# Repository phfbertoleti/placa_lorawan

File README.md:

# Placa LoRaWAN - repositório oficial

Este é o repositório oficial da placa LoRaWAN, placa de desenvolvimento para protótipos em Internet das Coisas com LoRaWAN, Bluetooth (BLE e clássico) e WiFi, fazendo uso do módulo Heltec wifi LoRa V1.

Este projeto é totalmente open-source (licença: MIT).

## Princípio de funcionamento

Essa placa tem objetivo de facilitar o desenvolvimento de protótipos em Internet das Coisas. A melhor forma encontrada para facilitar isso, foi disponibilizar conexões / soquetes para módulo de controle (Heltec wifi LoRa V1) e módulos sensores, conforme a seguir:

* Módulo MPU6050
* Módulo BMP180
* Módulo INA219
* Módulo MQ-2

Para comunicação com módulos (exemplo: GPS) e microcontroladores externos, a placa conta ainda com uma interface UART (níveis 3V3 e 5V, selecionável por jumper / ponte soldada na placa) e uma interface I²C (nível 3V3).

Além disso, essa placa permite o uso do módulo de controle Heltec wifi LoRa V1 com bateria (LiPo ou Li-Ion, de 1 célula), permitindo também a recarga e medição da tensão da mesma.

Isso significa que mesmo que você possua pouca experiência com eletrônica e soldagem, conseguirá facilmente montar e utilizar a placa.

## Funcionalidades

Esta placa, usada juntamente com um módulo Heltec wifi LoRa V1 e os sensores que a placa suporta, compreende as seguintes funcionaliades:
 
* Conectividades wifi, Bluetooth (BLE e clássico), LoRa e LoRaWAN.
* Medição de temperatura
* Medição de pressão barométrica
* Medição de aceleração (3 eixos)
* Giroscópio (3 eixos)
* Tensão e corrente DC
* Detecção de gases inflamávei e fumaça
* Display OLED 0.96" (azul)

Além disso, a placa possui conector para alimentação através de energias renováveis (solar, eólica ou hidráulica), com tensão de alimentação de até 15V.

## O que está disponivel neste repositório?

Resposta curta: 100% do projeto. Ou seja:

* Projeto completo de hardware (feito no KiCad 5.1.5)
* Arquivos gerber, já nos padrões para fabricação exigidos pela JLCPCB (www.jlcpcb.com)
* Softwares de exemplo (todos feitos na Arduino IDE, fazendo uso de bibliotecas populares e consagradas)
* Lista de materiais (BOM)
* Bibliotecas e footprints KiCad (para transistor FQP30N06L e Heltec wifi LoRa V1, sendo este último desenhado por mim).

Para ver a BOM interativa, [clique aqui](https://htmlpreview.github.io/?https://github.com/phfbertoleti/placa_lorawan/blob/master/BOM/ibom.html)

## Desejo contribuir com novas funcionalidades ou correções. Sou bem vindo?

Claro. Sinta-se a vontade para contribuir com o projeto. Toda melhoria é bem vinda!

## Gostei do seu trabalho. Onde consigo mais coisas publicadas por você?

Visite meu [site pessoal](http://www.pedrobertoleti.com.br) para ter acesso a quase tudo que publico no Brasil e exterior.

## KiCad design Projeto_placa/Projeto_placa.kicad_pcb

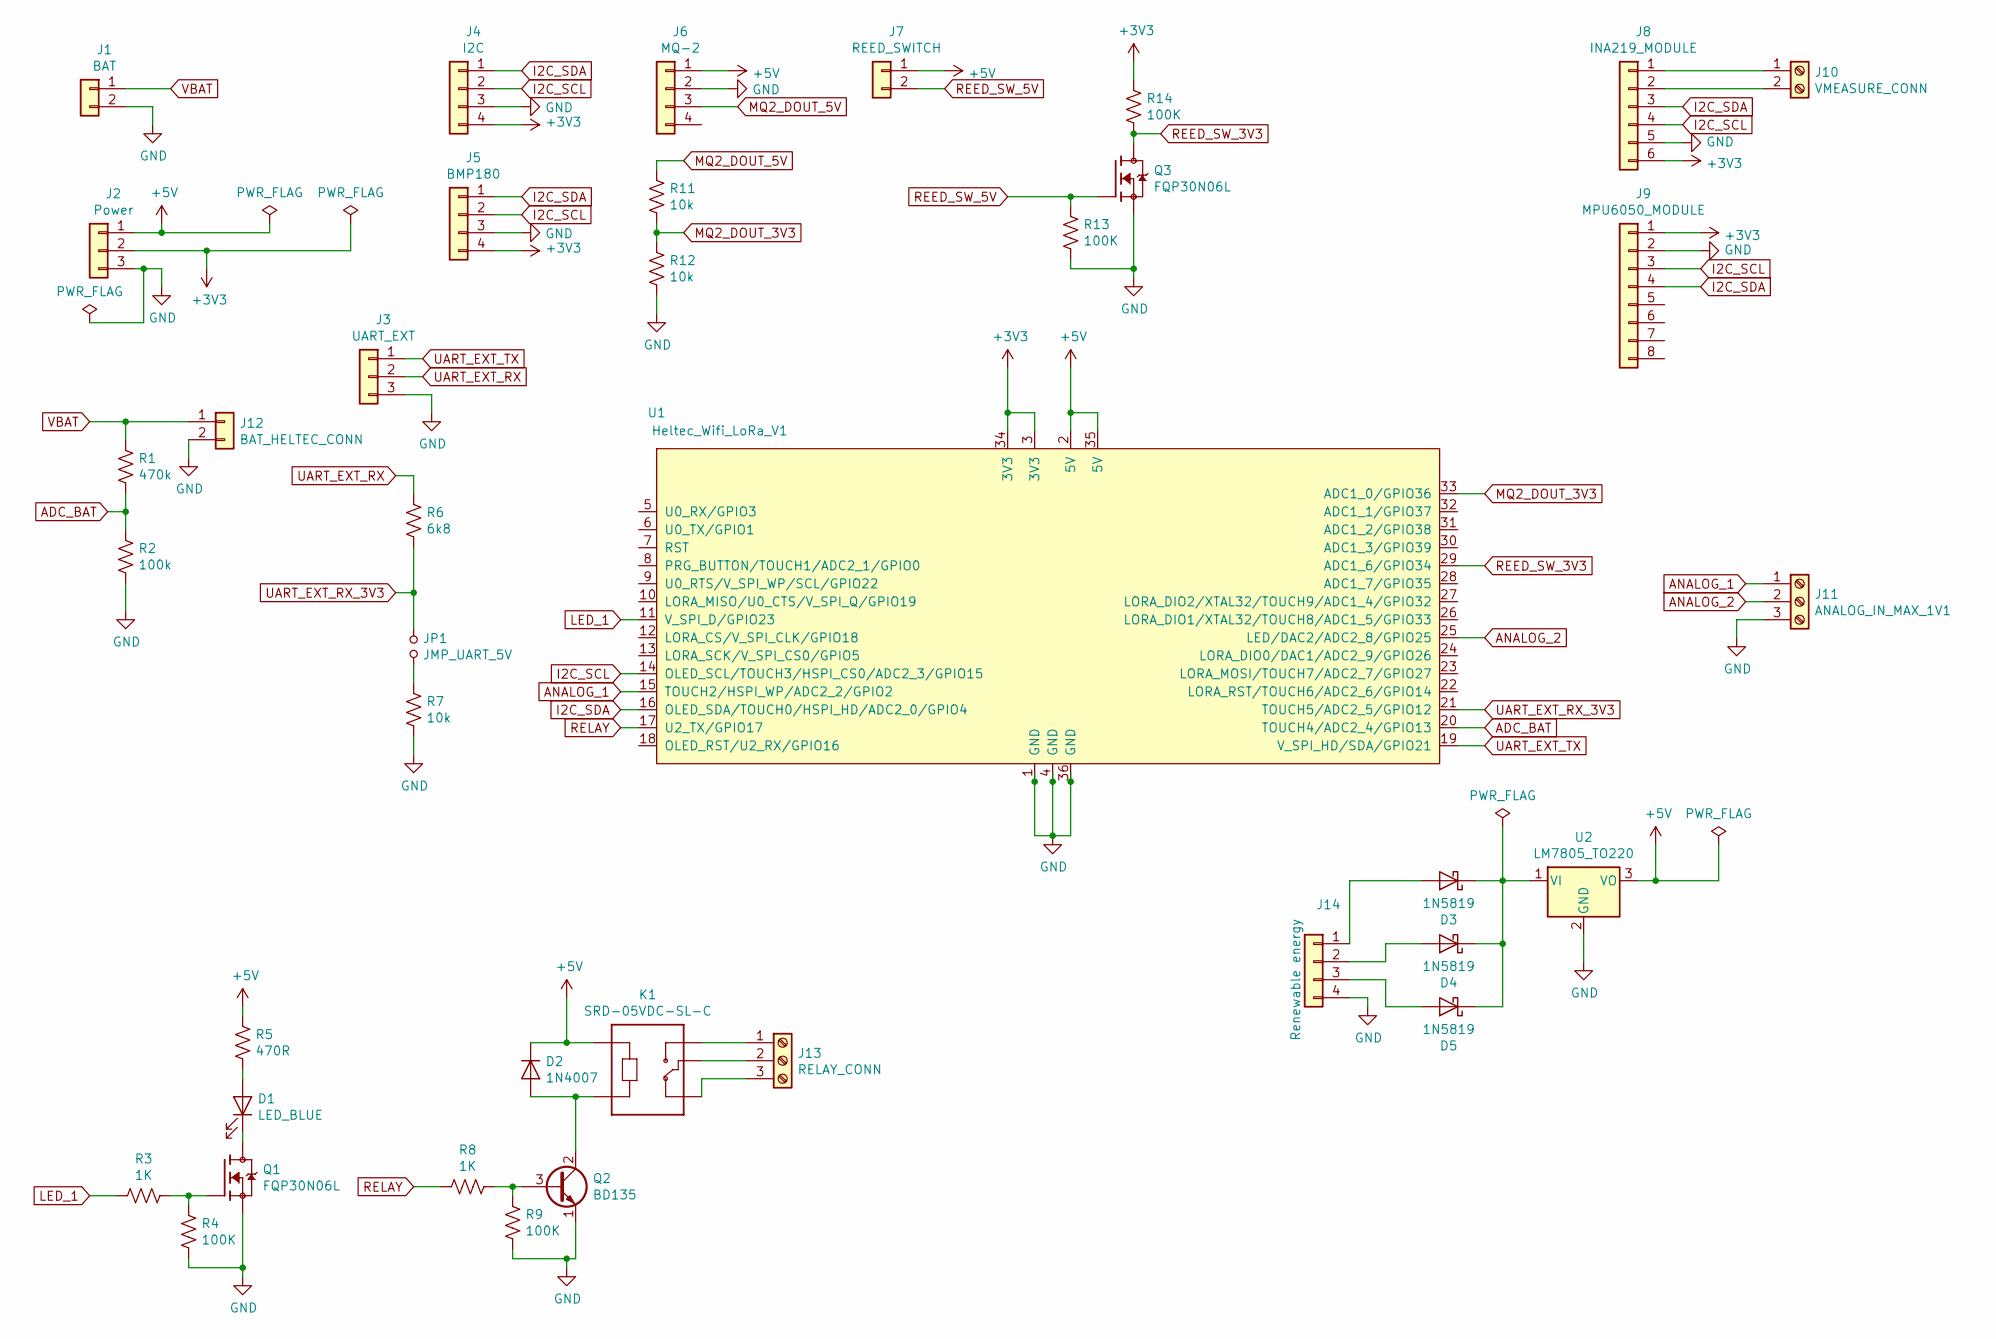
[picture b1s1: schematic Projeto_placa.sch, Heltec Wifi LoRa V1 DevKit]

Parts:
D1: LED_BLUE; LED_D5.0mm_Clear
D2: 1N4007; D_DO-41_SOD81_P10.16mm_Horizontal
D3, D4, D5: 1N5819; D_DO-41_SOD81_P10.16mm_Horizontal
J1: BAT; PinHeader_1x02_P2.54mm_Vertical
J2: Power; PinHeader_1x03_P2.54mm_Vertical
J3: UART_EXT; PinSocket_1x03_P2.54mm_Vertical
J4: I2C; PinSocket_1x04_P2.54mm_Vertical
J5: BMP180; PinSocket_1x04_P2.54mm_Vertical
J6: MQ-2; PinSocket_1x04_P2.54mm_Vertical
J7: REED_SWITCH; PinSocket_1x02_P2.54mm_Vertical
J8: INA219_MODULE; PinSocket_1x06_P2.54mm_Vertical
J9: MPU6050_MODULE; PinSocket_1x08_P2.54mm_Vertical
J10: VMEASURE_CONN; PhoenixContact_MCV_1,5_2-G-5.08_1x02_P5.08mm_Vertical
J11: ANALOG_IN_MAX_1V1; PhoenixContact_MCV_1,5_3-G-5.08_1x03_P5.08mm_Vertical
J12: BAT_HELTEC_CONN; PinSocket_1x02_P2.54mm_Vertical
J13: RELAY_CONN; PhoenixContact_MCV_1,5_3-G-5.08_1x03_P5.08mm_Vertical
J14: Renewable energy; PinSocket_1x04_P2.54mm_Vertical
JP1: JMP_UART_5V; SolderJumper-2_P1.3mm_Open_Pad1.0x1.5mm
K1: SRD-05VDC-SL-C; RELAY_SRD-05VDC-SL-C
Q1, Q3: FQP30N06L; TO220V
Q2: BD135; TO-126-3_Vertical
R1: 470k; R_Axial_DIN0207_L6.3mm_D2.5mm_P15.24mm_Horizontal
R2: 100k; R_Axial_DIN0207_L6.3mm_D2.5mm_P15.24mm_Horizontal
R3, R8: 1K; R_Axial_DIN0207_L6.3mm_D2.5mm_P15.24mm_Horizontal
R4, R9, R13, R14: 100K; R_Axial_DIN0207_L6.3mm_D2.5mm_P15.24mm_Horizontal
R5: 470R; R_Axial_DIN0207_L6.3mm_D2.5mm_P15.24mm_Horizontal
R6: 6k8; R_Axial_DIN0207_L6.3mm_D2.5mm_P15.24mm_Horizontal
R7, R11, R12: 10k; R_Axial_DIN0207_L6.3mm_D2.5mm_P15.24mm_Horizontal
U1: Heltec_Wifi_LoRa_V1; Heltec_WiFi_LoRa_V1
U2: LM7805_TO220; TO-220-3_Vertical

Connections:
+3V3: J2.2, J4.4, J5.4, J8.6, J9.1, R14.1, U1.3 (3V3), U1.34 (3V3)
+5V: D2.1 (K), J2.1, J6.1, J7.1, K1.A1, R5.1, U1.2 (5V), U1.35 (5V), U2.3 (VO)
ADC_BAT: R1.2, R2.1, U1.20 (TOUCH4/ADC2_4/GPIO13)
ANALOG_1: J11.1, U1.15 (TOUCH2/HSPI_WP/ADC2_2/GPIO2)
ANALOG_2: J11.2, U1.25 (LED/DAC2/ADC2_8/GPIO25)
GND: J1.2, J2.3, J3.3, J4.3, J5.3, J6.2, J8.5, J9.2, J11.3, J12.2, J14.4, Q1.3, Q2.1 (E), Q3.3, R2.2, R4.2, R7.2, R9.2, R12.2, R13.2, U1.1 (GND), U1.4 (GND), U1.36 (GND), U2.2 (GND)
I2C_SCL: J4.2, J5.2, J8.4, J9.3, U1.14 (OLED_SCL/TOUCH3/HSPI_CS0/ADC2_3/GPIO15)
I2C_SDA: J4.1, J5.1, J8.3, J9.4, U1.16 (OLED_SDA/TOUCH0/HSPI_HD/ADC2_0/GPIO4)
LED_1: R3.2, U1.11 (V_SPI_D/GPIO23)
MQ2_DOUT_3V3: R11.2, R12.1, U1.33 (ADC1_0/GPIO36)
MQ2_DOUT_5V: J6.3, R11.1
unnamed: D1.1 (K), Q1.2
unnamed: D1.2 (A), R5.2
unnamed: D2.2 (A), K1.A2, Q2.2 (C)
unnamed: D3.1 (K), D4.1 (K), D5.1 (K), U2.1 (VI)
unnamed: D3.2 (A), J14.1
unnamed: D4.2 (A), J14.2
unnamed: D5.2 (A), J14.3
unnamed: J8.1, J10.1
unnamed: J8.2, J10.2
unnamed: J13.1, K1.NO
unnamed: J13.2, K1.COM
unnamed: J13.3, K1.NC
unnamed: JP1.2, R7.1
unnamed: Q1.1, R3.1, R4.1
unnamed: Q2.3 (B), R8.1, R9.1
REED_SW_3V3: Q3.2, R14.2, U1.29 (ADC1_6/GPIO34)
REED_SW_5V: J7.2, Q3.1, R13.1
RELAY: R8.2, U1.17 (U2_TX/GPIO17)
UART_EXT_RX: J3.2, R6.1
UART_EXT_RX_3V3: JP1.1, R6.2, U1.21 (TOUCH5/ADC2_5/GPIO12)
UART_EXT_TX: J3.1, U1.19 (V_SPI_HD/SDA/GPIO21)
VBAT: J1.1, J12.1, R1.1

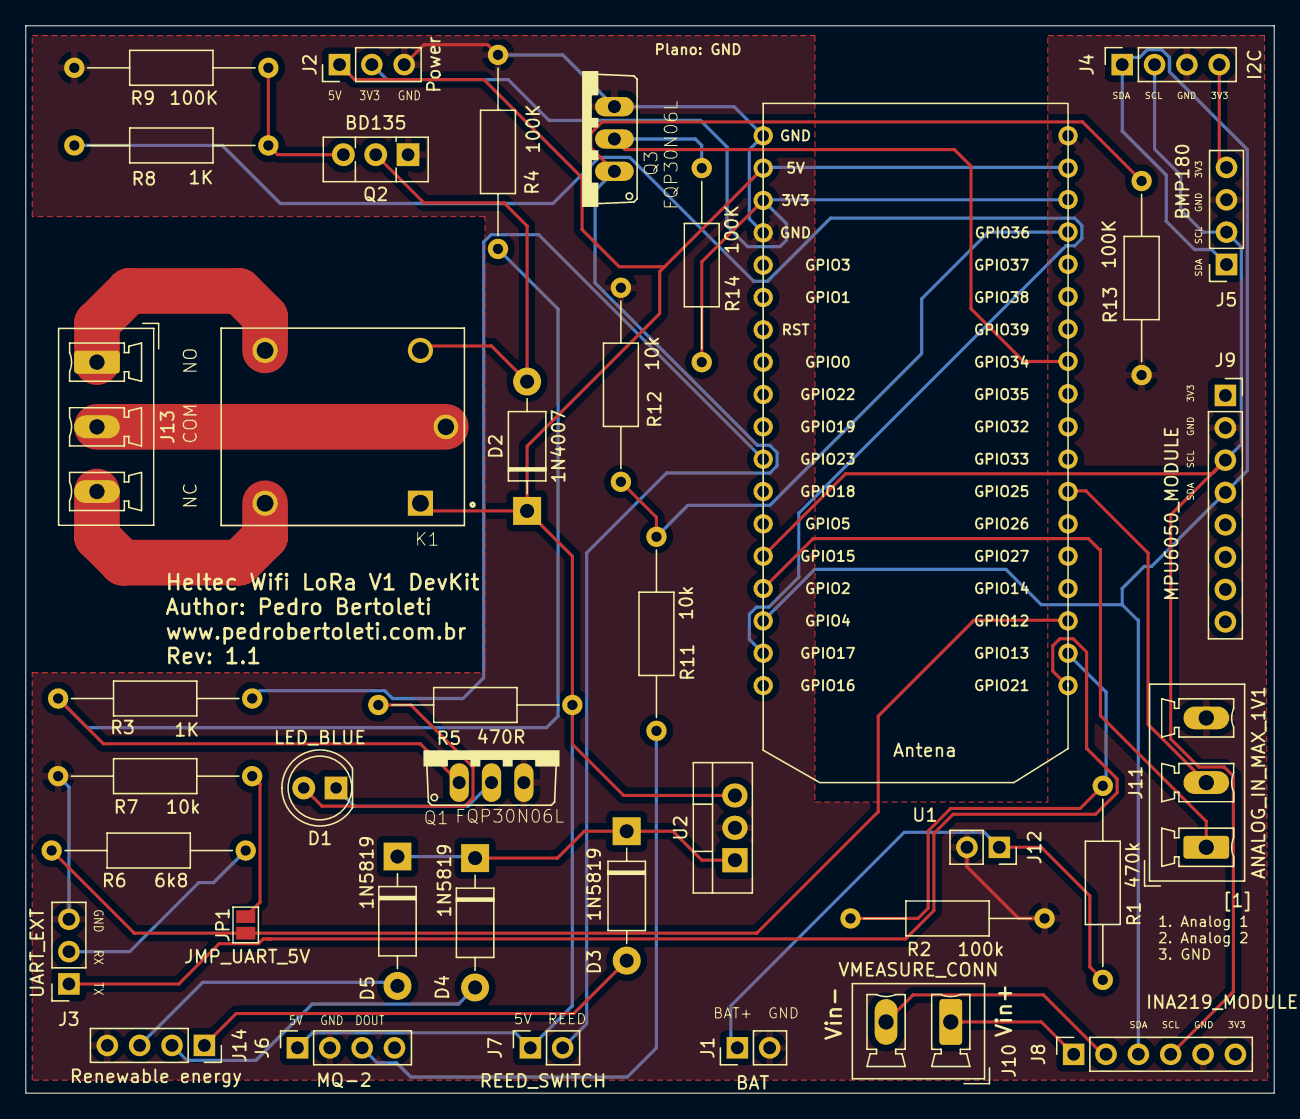
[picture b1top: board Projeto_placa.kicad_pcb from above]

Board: 2 copper layers, 98.0 x 83.8 mm, 39 parts (0 on the bottom side), 33 nets.

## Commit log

2020-10-30 Primeiro commit
2020-10-30 correções no readme
2020-10-30 adicionada visualização da PCB (3D)
2020-10-30 atualização do README
